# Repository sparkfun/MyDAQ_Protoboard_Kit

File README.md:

MyDAQ Protoboard Kit
====================

[  
*myDAQ Protoboard Kit(DEV-10705)*](https://www.sparkfun.com/products/10705)

This kit is designed to connect directly to the National Instruments myDAQ measurement and control tool. 

Repository Contents
-------------------
* **/Hardware** - All Eagle design files (.brd, .sch, .STL)

License Information
-------------------
The hardware is released under [Creative Commons Share-alike 3.0](http://creativecommons.org/licenses/by-sa/3.0/).

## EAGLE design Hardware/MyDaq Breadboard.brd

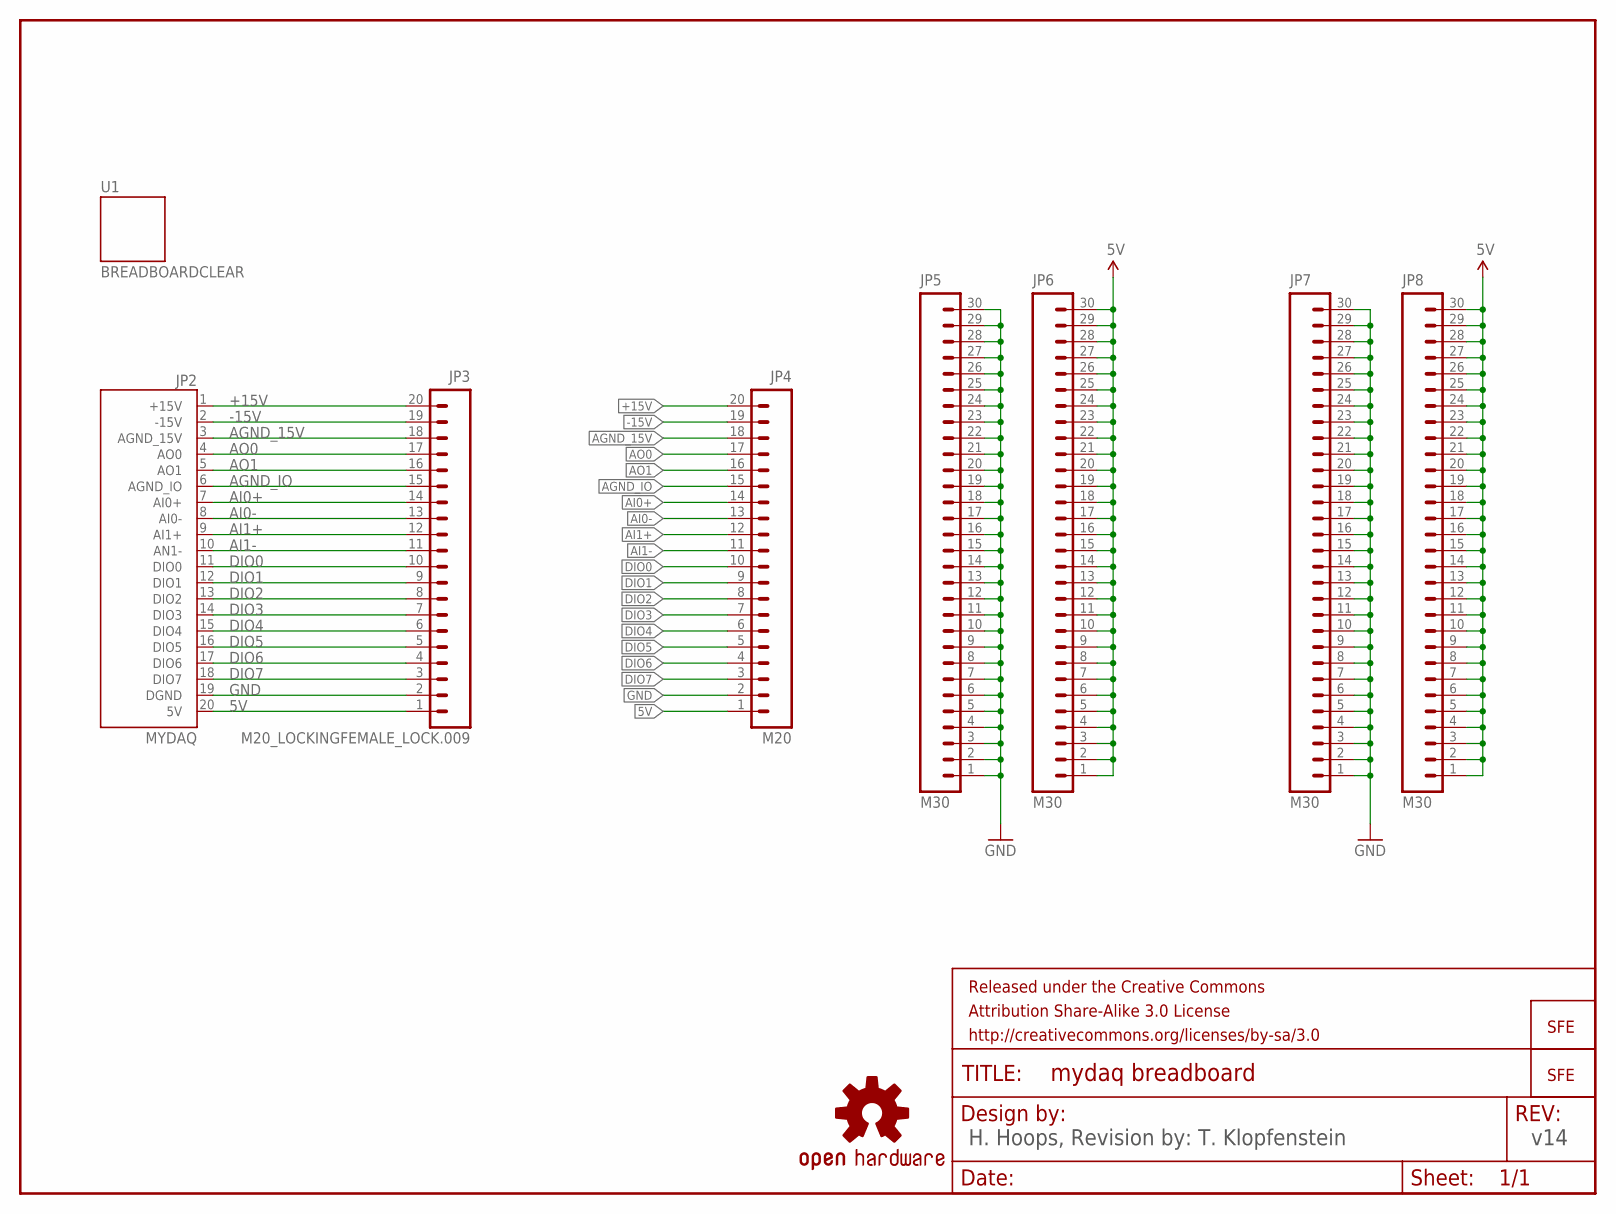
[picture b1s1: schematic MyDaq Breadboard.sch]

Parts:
FRAME2: FRAME-LETTER; CREATIVE_COMMONS
JP1: LOGO-SFENEW; SFE-NEW-WEBLOGO
JP2: MYDAQ; 3.81MM_TERMINAL_BLOCK_FEMALE_LOCKING
JP3: M20_LOCKINGFEMALE_LOCK.009; 1X20_LOCK
JP4: M20; 1X20
JP5, JP6, JP7, JP8: M30; 1X30
LOGO1: OSHW-LOGOL; OSHW-LOGO-L
LOGO2: LOGO-SFESK; SFE-LOGO-FLAME
U1: BREADBOARDCLEAR; BREADBOARD_CLEAR

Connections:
5V: JP2.20 (5V), JP3.1, JP4.1, JP6.1, JP6.2, JP6.3, JP6.4, JP6.5, JP6.6, JP6.7, JP6.8, JP6.9, JP6.10, JP6.11, JP6.12, JP6.13, JP6.14, JP6.15, JP6.16, JP6.17, JP6.18, JP6.19, JP6.20, JP6.21, JP6.22, JP6.23, JP6.24, JP6.25, JP6.26, JP6.27, JP6.28, JP6.29, JP6.30, JP8.1, JP8.2, JP8.3, JP8.4, JP8.5, JP8.6, JP8.7, JP8.8, JP8.9, JP8.10, JP8.11, JP8.12, JP8.13, JP8.14, JP8.15, JP8.16, JP8.17, JP8.18, JP8.19, JP8.20, JP8.21, JP8.22, JP8.23, JP8.24, JP8.25, JP8.26, JP8.27, JP8.28, JP8.29, JP8.30
+15V: JP2.1 (+15V), JP3.20, JP4.20
-15V: JP2.2 (-15V), JP3.19, JP4.19
AGND_15V: JP2.3 (AGND_15V), JP3.18, JP4.18
AGND_IO: JP2.6 (AGND_IO), JP3.15, JP4.15
AI0+: JP2.7 (AI0+), JP3.14, JP4.14
AI0-: JP2.8 (AI0-), JP3.13, JP4.13
AI1+: JP2.9 (AI1+), JP3.12, JP4.12
AI1-: JP2.10 (AN1-), JP3.11, JP4.11
AO0: JP2.4 (AO0), JP3.17, JP4.17
AO1: JP2.5 (AO1), JP3.16, JP4.16
DIO0: JP2.11 (DIO0), JP3.10, JP4.10
DIO1: JP2.12 (DIO1), JP3.9, JP4.9
DIO2: JP2.13 (DIO2), JP3.8, JP4.8
DIO3: JP2.14 (DIO3), JP3.7, JP4.7
DIO4: JP2.15 (DIO4), JP3.6, JP4.6
DIO5: JP2.16 (DIO5), JP3.5, JP4.5
DIO6: JP2.17 (DIO6), JP3.4, JP4.4
DIO7: JP2.18 (DIO7), JP3.3, JP4.3
GND: JP2.19 (DGND), JP3.2, JP4.2, JP5.1, JP5.2, JP5.3, JP5.4, JP5.5, JP5.6, JP5.7, JP5.8, JP5.9, JP5.10, JP5.11, JP5.12, JP5.13, JP5.14, JP5.15, JP5.16, JP5.17, JP5.18, JP5.19, JP5.20, JP5.21, JP5.22, JP5.23, JP5.24, JP5.25, JP5.26, JP5.27, JP5.28, JP5.29, JP5.30, JP7.1, JP7.2, JP7.3, JP7.4, JP7.5, JP7.6, JP7.7, JP7.8, JP7.9, JP7.10, JP7.11, JP7.12, JP7.13, JP7.14, JP7.15, JP7.16, JP7.17, JP7.18, JP7.19, JP7.20, JP7.21, JP7.22, JP7.23, JP7.24, JP7.25, JP7.26, JP7.27, JP7.28, JP7.29, JP7.30

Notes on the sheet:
H. Hoops, Revision by: T. Klopfenstein
v14

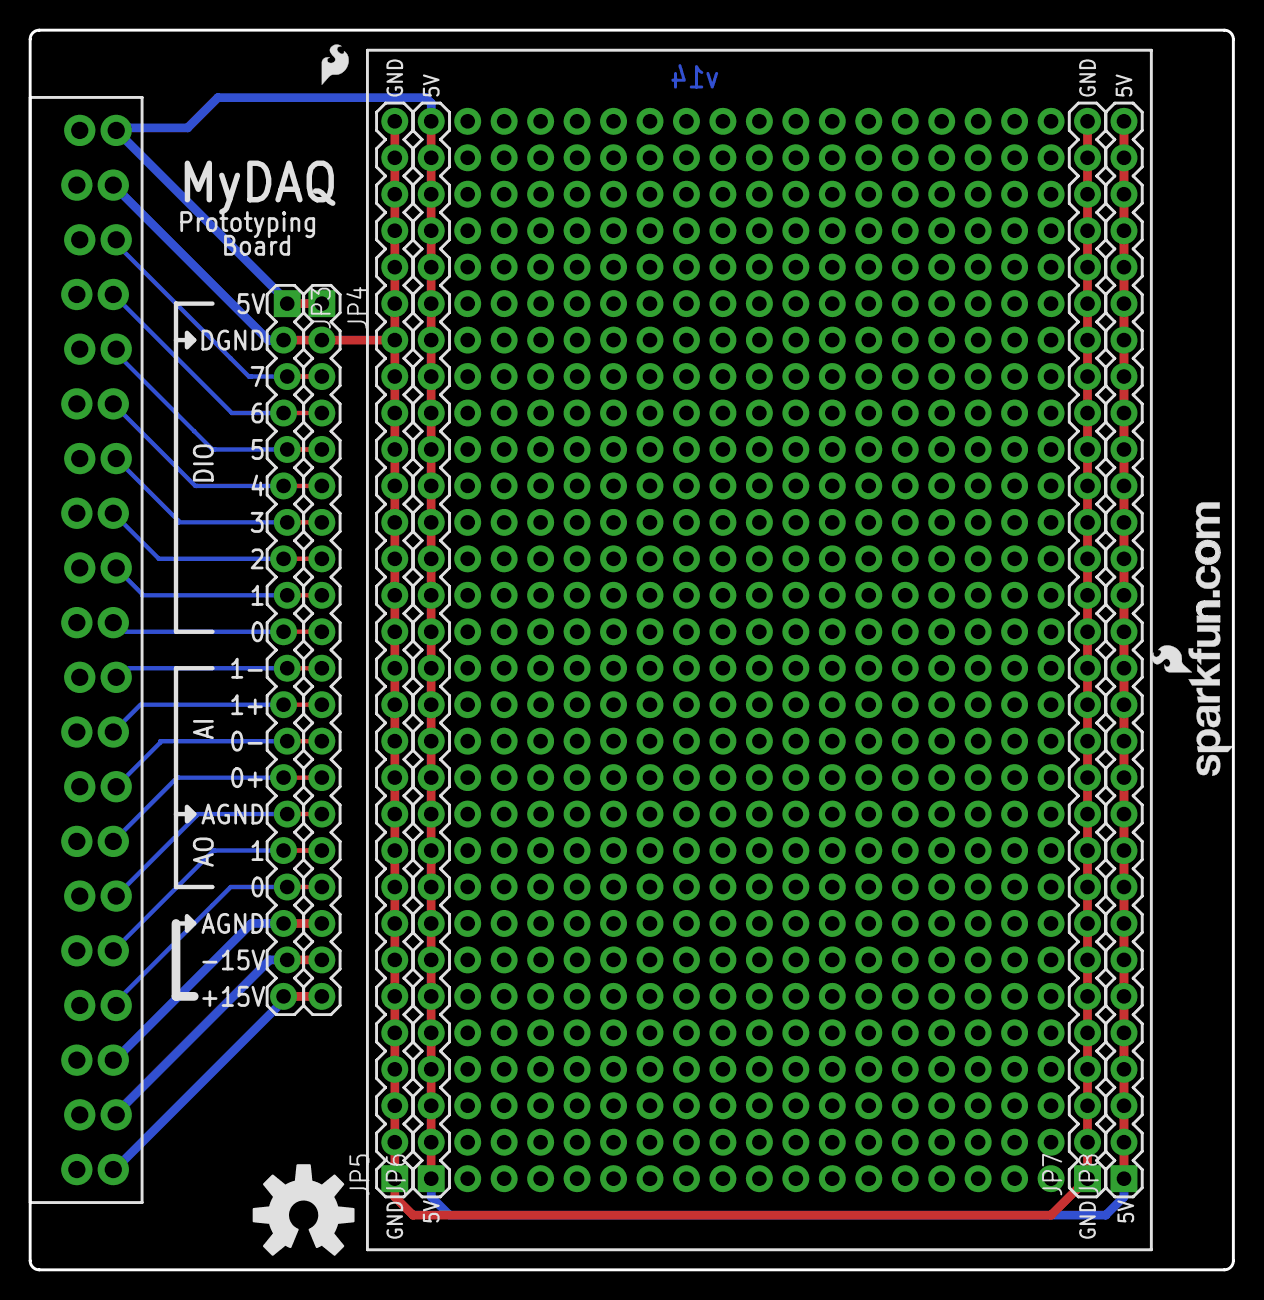
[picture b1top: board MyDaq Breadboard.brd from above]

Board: 2 copper layers, 83.8 x 86.4 mm, 12 parts (0 on the bottom side), 20 nets.

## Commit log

2013-07-09 Updated board to OSHW/changed headers for Production
2013-07-15 Centered logos and changed revision to symbol

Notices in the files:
parts and their libraries:
SparkFun-Aesthetics: Licensing: CC v3.0 Share-Alike You are welcome to use this library for commercial purposes.
SparkFun-Aesthetics: Released under the Creative Commons Attribution Share-Alike 3.0 License
SparkFun-Aesthetics: Released under the Creative Commons
